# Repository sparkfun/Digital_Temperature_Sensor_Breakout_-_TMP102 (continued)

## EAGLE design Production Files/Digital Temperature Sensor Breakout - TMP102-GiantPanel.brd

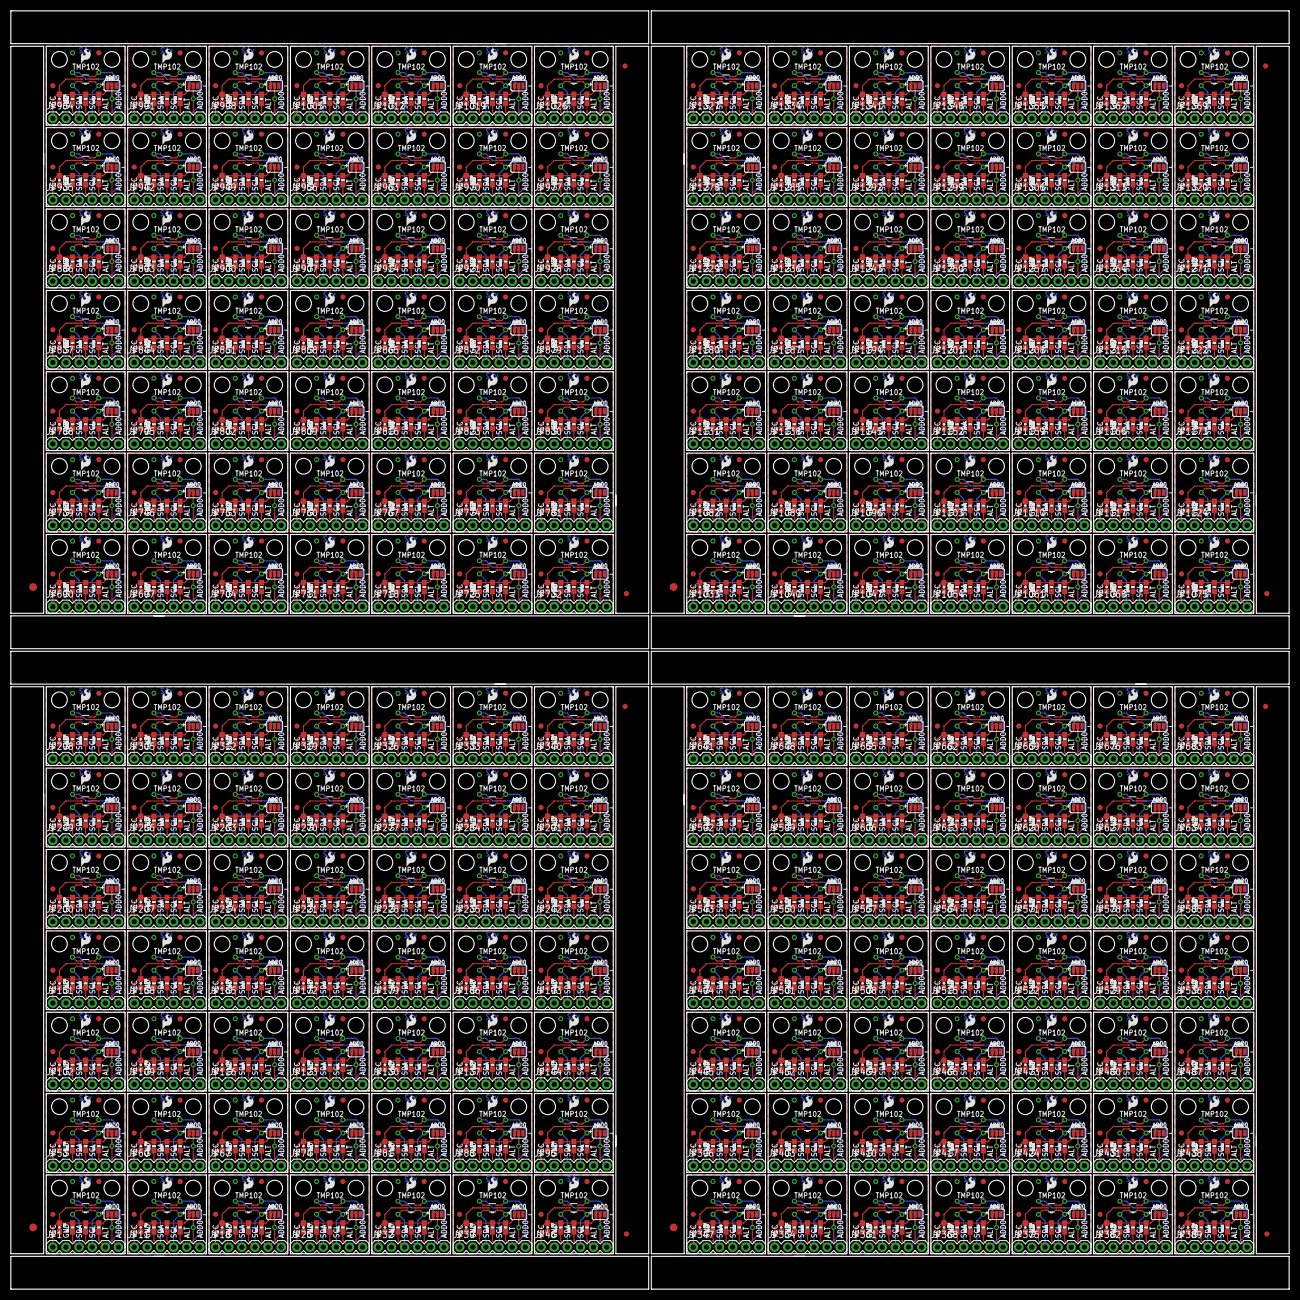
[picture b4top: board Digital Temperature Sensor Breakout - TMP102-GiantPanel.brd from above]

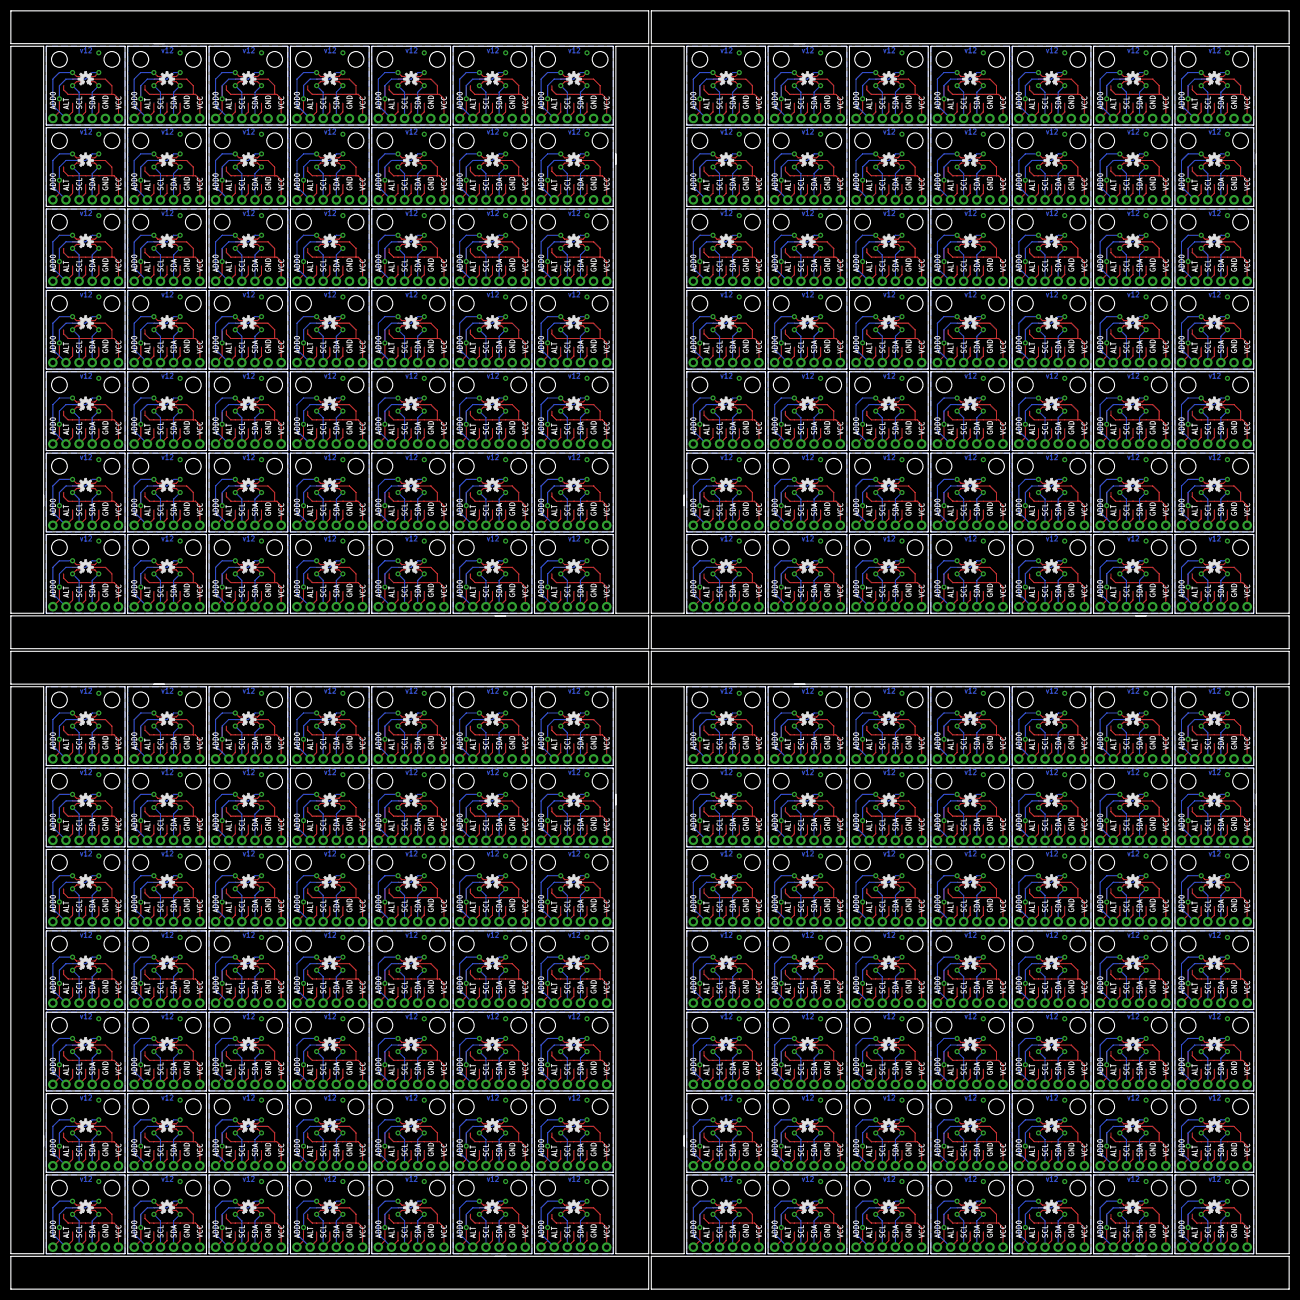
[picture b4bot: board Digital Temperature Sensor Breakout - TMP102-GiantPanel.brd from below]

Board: 2 copper layers, 247.4 x 247.4 mm, 2560 parts (196 on the bottom side), 1176 nets.

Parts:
C1, C2, C3, C4, C5, C6, C7, C8, C9, C10, C11, C12, C13, C14, C15, C16, C17, C18, C19, C20, C21, C22, C23, C24, C25, C26, C27, C28, C29, C30, C31, C32, C33, C34, C35, C36, C37, C38, C39, C40, C41, C42, C43, C44, C45, C46, C47, C48, C49, C50, C51, C52, C53, C54, C55, C56, C57, C58, C59, C60, C61, C62, C63, C64, C65, C66, C67, C68, C69, C70, C71, C72, C73, C74, C75, C76, C77, C78, C79, C80, C81, C82, C83, C84, C85, C86, C87, C88, C89, C90, C91, C92, C93, C94, C95, C96, C97, C98, C99, C100, C101, C102, C103, C104, C105, C106, C107, C108, C109, C110, C111, C112, C113, C114, C115, C116, C117, C118, C119, C120, C121, C122, C123, C124, C125, C126, C127, C128, C129, C130, C131, C132, C133, C134, C135, C136, C137, C138, C139, C140, C141, C142, C143, C144, C145, C146, C147, C148, C149, C150, C151, C152, C153, C154, C155, C156, C157, C158, C159, C160, C161, C162, C163, C164, C165, C166, C167, C168, C169, C170, C171, C172, C173, C174, C175, C176, C177, C178, C179, C180, C181, C182, C183, C184, C185, C186, C187, C188, C189, C190, C191, C192, C193, C194, C195, C196: 0.1uF; 0603-CAP
E$1, E$6, E$9, E$12: FIDUCIAL-1.5X3
E$2, E$3, E$4, E$5, E$7, E$8, E$10, E$11: FIDUCIAL-1X2
JP1, JP11, JP18, JP25, JP32, JP39, JP46, JP53, JP60, JP67, JP74, JP81, JP88, JP95, JP102, JP109, JP116, JP123, JP130, JP137, JP144, JP151, JP158, JP165, JP172, JP179, JP186, JP193, JP200, JP207, JP214, JP221, JP228, JP235, JP242, JP249, JP256, JP263, JP270, JP277, JP284, JP291, JP298, JP305, JP312, JP319, JP326, JP333, JP340, JP347, JP354, JP361, JP368, JP375, JP382, JP389, JP396, JP403, JP410, JP417, JP424, JP431, JP438, JP445, JP452, JP459, JP466, JP473, JP480, JP487, JP494, JP501, JP508, JP515, JP522, JP529, JP536, JP543, JP550, JP557, JP564, JP571, JP578, JP585, JP592, JP599, JP606, JP613, JP620, JP627, JP634, JP641, JP648, JP655, JP662, JP669, JP676, JP683, JP690, JP697, JP704, JP711, JP718, JP725, JP732, JP739, JP746, JP753, JP760, JP767, JP774, JP781, JP788, JP795, JP802, JP809, JP816, JP823, JP830, JP837, JP844, JP851, JP858, JP865, JP872, JP879, JP886, JP893, JP900, JP907, JP914, JP921, JP928, JP935, JP942, JP949, JP956, JP963, JP970, JP977, JP984, JP991, JP998, JP1005, JP1012, JP1019, JP1026, JP1033, JP1040, JP1047, JP1054, JP1061, JP1068, JP1075, JP1082, JP1089, JP1096, JP1103, JP1110, JP1117, JP1124, JP1131, JP1138, JP1145, JP1152, JP1159, JP1166, JP1173, JP1180, JP1187, JP1194, JP1201, JP1208, JP1215, JP1222, JP1229, JP1236, JP1243, JP1250, JP1257, JP1264, JP1271, JP1278, JP1285, JP1292, JP1299, JP1306, JP1313, JP1320, JP1327, JP1334, JP1341, JP1348, JP1355, JP1362, JP1369: 1X06
JP2, JP12, JP19, JP26, JP33, JP40, JP47, JP54, JP61, JP68, JP75, JP82, JP89, JP96, JP103, JP110, JP117, JP124, JP131, JP138, JP145, JP152, JP159, JP166, JP173, JP180, JP187, JP194, JP201, JP208, JP215, JP222, JP229, JP236, JP243, JP250, JP257, JP264, JP271, JP278, JP285, JP292, JP299, JP306, JP313, JP320, JP327, JP334, JP341, JP348, JP355, JP362, JP369, JP376, JP383, JP390, JP397, JP404, JP411, JP418, JP425, JP432, JP439, JP446, JP453, JP460, JP467, JP474, JP481, JP488, JP495, JP502, JP509, JP516, JP523, JP530, JP537, JP544, JP551, JP558, JP565, JP572, JP579, JP586, JP593, JP600, JP607, JP614, JP621, JP628, JP635, JP642, JP649, JP656, JP663, JP670, JP677, JP684, JP691, JP698, JP705, JP712, JP719, JP726, JP733, JP740, JP747, JP754, JP761, JP768, JP775, JP782, JP789, JP796, JP803, JP810, JP817, JP824, JP831, JP838, JP845, JP852, JP859, JP866, JP873, JP880, JP887, JP894, JP901, JP908, JP915, JP922, JP929, JP936, JP943, JP950, JP957, JP964, JP971, JP978, JP985, JP992, JP999, JP1006, JP1013, JP1020, JP1027, JP1034, JP1041, JP1048, JP1055, JP1062, JP1069, JP1076, JP1083, JP1090, JP1097, JP1104, JP1111, JP1118, JP1125, JP1132, JP1139, JP1146, JP1153, JP1160, JP1167, JP1174, JP1181, JP1188, JP1195, JP1202, JP1209, JP1216, JP1223, JP1230, JP1237, JP1244, JP1251, JP1258, JP1265, JP1272, JP1279, JP1286, JP1293, JP1300, JP1307, JP1314, JP1321, JP1328, JP1335, JP1342, JP1349, JP1356, JP1363, JP1370: JUMPER-32-3; SJ_3_PASTE2&3
JP3, JP8, JP15, JP22, JP29, JP36, JP43, JP50, JP57, JP64, JP71, JP78, JP85, JP92, JP99, JP106, JP113, JP120, JP127, JP134, JP141, JP148, JP155, JP162, JP169, JP176, JP183, JP190, JP197, JP204, JP211, JP218, JP225, JP232, JP239, JP246, JP253, JP260, JP267, JP274, JP281, JP288, JP295, JP302, JP309, JP316, JP323, JP330, JP337, JP344, JP351, JP358, JP365, JP372, JP379, JP386, JP393, JP400, JP407, JP414, JP421, JP428, JP435, JP442, JP449, JP456, JP463, JP470, JP477, JP484, JP491, JP498, JP505, JP512, JP519, JP526, JP533, JP540, JP547, JP554, JP561, JP568, JP575, JP582, JP589, JP596, JP603, JP610, JP617, JP624, JP631, JP638, JP645, JP652, JP659, JP666, JP673, JP680, JP687, JP694, JP701, JP708, JP715, JP722, JP729, JP736, JP743, JP750, JP757, JP764, JP771, JP778, JP785, JP792, JP799, JP806, JP813, JP820, JP827, JP834, JP841, JP848, JP855, JP862, JP869, JP876, JP883, JP890, JP897, JP904, JP911, JP918, JP925, JP932, JP939, JP946, JP953, JP960, JP967, JP974, JP981, JP988, JP995, JP1002, JP1009, JP1016, JP1023, JP1030, JP1037, JP1044, JP1051, JP1058, JP1065, JP1072, JP1079, JP1086, JP1093, JP1100, JP1107, JP1114, JP1121, JP1128, JP1135, JP1142, JP1149, JP1156, JP1163, JP1170, JP1177, JP1184, JP1191, JP1198, JP1205, JP1212, JP1219, JP1226, JP1233, JP1240, JP1247, JP1254, JP1261, JP1268, JP1275, JP1282, JP1289, JP1296, JP1303, JP1310, JP1317, JP1324, JP1331, JP1338, JP1345, JP1352, JP1359, JP1366: LOGO-SFESK; SFE-LOGO-FLAME
JP4, JP5, JP9, JP10, JP16, JP17, JP23, JP24, JP30, JP31, JP37, JP38, JP44, JP45, JP51, JP52, JP58, JP59, JP65, JP66, JP72, JP73, JP79, JP80, JP86, JP87, JP93, JP94, JP100, JP101, JP107, JP108, JP114, JP115, JP121, JP122, JP128, JP129, JP135, JP136, JP142, JP143, JP149, JP150, JP156, JP157, JP163, JP164, JP170, JP171, JP177, JP178, JP184, JP185, JP191, JP192, JP198, JP199, JP205, JP206, JP212, JP213, JP219, JP220, JP226, JP227, JP233, JP234, JP240, JP241, JP247, JP248, JP254, JP255, JP261, JP262, JP268, JP269, JP275, JP276, JP282, JP283, JP289, JP290, JP296, JP297, JP303, JP304, JP310, JP311, JP317, JP318, JP324, JP325, JP331, JP332, JP338, JP339, JP345, JP346, JP352, JP353, JP359, JP360, JP366, JP367, JP373, JP374, JP380, JP381, JP387, JP388, JP394, JP395, JP401, JP402, JP408, JP409, JP415, JP416, JP422, JP423, JP429, JP430, JP436, JP437, JP443, JP444, JP450, JP451, JP457, JP458, JP464, JP465, JP471, JP472, JP478, JP479, JP485, JP486, JP492, JP493, JP499, JP500, JP506, JP507, JP513, JP514, JP520, JP521, JP527, JP528, JP534, JP535, JP541, JP542, JP548, JP549, JP555, JP556, JP562, JP563, JP569, JP570, JP576, JP577, JP583, JP584, JP590, JP591, JP597, JP598, JP604, JP605, JP611, JP612, JP618, JP619, JP625, JP626, JP632, JP633, JP639, JP640, JP646, JP647, JP653, JP654, JP660, JP661, JP667, JP668, JP674, JP675, JP681, JP682, JP688, JP689, JP695, JP696, JP702, JP703, JP709, JP710, JP716, JP717, JP723, JP724, JP730, JP731, JP737, JP738, JP744, JP745, JP751, JP752, JP758, JP759, JP765, JP766, JP772, JP773, JP779, JP780, JP786, JP787, JP793, JP794, JP800, JP801, JP807, JP808, JP814, JP815, JP821, JP822, JP828, JP829, JP835, JP836, JP842, JP843, JP849, JP850, JP856, JP857, JP863, JP864, JP870, JP871, JP877, JP878, JP884, JP885, JP891, JP892, JP898, JP899, JP905, JP906, JP912, JP913, JP919, JP920, JP926, JP927, JP933, JP934, JP940, JP941, JP947, JP948, JP954, JP955, JP961, JP962, JP968, JP969, JP975, JP976, JP982, JP983, JP989, JP990, JP996, JP997, JP1003, JP1004, JP1010, JP1011, JP1017, JP1018, JP1024, JP1025, JP1031, JP1032, JP1038, JP1039, JP1045, JP1046, JP1052, JP1053, JP1059, JP1060, JP1066, JP1067, JP1073, JP1074, JP1080, JP1081, JP1087, JP1088, JP1094, JP1095, JP1101, JP1102, JP1108, JP1109, JP1115, JP1116, JP1122, JP1123, JP1129, JP1130, JP1136, JP1137, JP1143, JP1144, JP1150, JP1151, JP1157, JP1158, JP1164, JP1165, JP1171, JP1172, JP1178, JP1179, JP1185, JP1186, JP1192, JP1193, JP1199, JP1200, JP1206, JP1207, JP1213, JP1214, JP1220, JP1221, JP1227, JP1228, JP1234, JP1235, JP1241, JP1242, JP1248, JP1249, JP1255, JP1256, JP1262, JP1263, JP1269, JP1270, JP1276, JP1277, JP1283, JP1284, JP1290, JP1291, JP1297, JP1298, JP1304, JP1305, JP1311, JP1312, JP1318, JP1319, JP1325, JP1326, JP1332, JP1333, JP1339, JP1340, JP1346, JP1347, JP1353, JP1354, JP1360, JP1361, JP1367, JP1368: FIDUCIAL1X2; FIDUCIAL-1X2
JP6, JP7, JP13, JP14, JP20, JP21, JP27, JP28, JP34, JP35, JP41, JP42, JP48, JP49, JP55, JP56, JP62, JP63, JP69, JP70, JP76, JP77, JP83, JP84, JP90, JP91, JP97, JP98, JP104, JP105, JP111, JP112, JP118, JP119, JP125, JP126, JP132, JP133, JP139, JP140, JP146, JP147, JP153, JP154, JP160, JP161, JP167, JP168, JP174, JP175, JP181, JP182, JP188, JP189, JP195, JP196, JP202, JP203, JP209, JP210, JP216, JP217, JP223, JP224, JP230, JP231, JP237, JP238, JP244, JP245, JP251, JP252, JP258, JP259, JP265, JP266, JP272, JP273, JP279, JP280, JP286, JP287, JP293, JP294, JP300, JP301, JP307, JP308, JP314, JP315, JP321, JP322, JP328, JP329, JP335, JP336, JP342, JP343, JP349, JP350, JP356, JP357, JP363, JP364, JP370, JP371, JP377, JP378, JP384, JP385, JP391, JP392, JP398, JP399, JP405, JP406, JP412, JP413, JP419, JP420, JP426, JP427, JP433, JP434, JP440, JP441, JP447, JP448, JP454, JP455, JP461, JP462, JP468, JP469, JP475, JP476, JP482, JP483, JP489, JP490, JP496, JP497, JP503, JP504, JP510, JP511, JP517, JP518, JP524, JP525, JP531, JP532, JP538, JP539, JP545, JP546, JP552, JP553, JP559, JP560, JP566, JP567, JP573, JP574, JP580, JP581, JP587, JP588, JP594, JP595, JP601, JP602, JP608, JP609, JP615, JP616, JP622, JP623, JP629, JP630, JP636, JP637, JP643, JP644, JP650, JP651, JP657, JP658, JP664, JP665, JP671, JP672, JP678, JP679, JP685, JP686, JP692, JP693, JP699, JP700, JP706, JP707, JP713, JP714, JP720, JP721, JP727, JP728, JP734, JP735, JP741, JP742, JP748, JP749, JP755, JP756, JP762, JP763, JP769, JP770, JP776, JP777, JP783, JP784, JP790, JP791, JP797, JP798, JP804, JP805, JP811, JP812, JP818, JP819, JP825, JP826, JP832, JP833, JP839, JP840, JP846, JP847, JP853, JP854, JP860, JP861, JP867, JP868, JP874, JP875, JP881, JP882, JP888, JP889, JP895, JP896, JP902, JP903, JP909, JP910, JP916, JP917, JP923, JP924, JP930, JP931, JP937, JP938, JP944, JP945, JP951, JP952, JP958, JP959, JP965, JP966, JP972, JP973, JP979, JP980, JP986, JP987, JP993, JP994, JP1000, JP1001, JP1007, JP1008, JP1014, JP1015, JP1021, JP1022, JP1028, JP1029, JP1035, JP1036, JP1042, JP1043, JP1049, JP1050, JP1056, JP1057, JP1063, JP1064, JP1070, JP1071, JP1077, JP1078, JP1084, JP1085, JP1091, JP1092, JP1098, JP1099, JP1105, JP1106, JP1112, JP1113, JP1119, JP1120, JP1126, JP1127, JP1133, JP1134, JP1140, JP1141, JP1147, JP1148, JP1154, JP1155, JP1161, JP1162, JP1168, JP1169, JP1175, JP1176, JP1182, JP1183, JP1189, JP1190, JP1196, JP1197, JP1203, JP1204, JP1210, JP1211, JP1217, JP1218, JP1224, JP1225, JP1231, JP1232, JP1238, JP1239, JP1245, JP1246, JP1252, JP1253, JP1259, JP1260, JP1266, JP1267, JP1273, JP1274, JP1280, JP1281, JP1287, JP1288, JP1294, JP1295, JP1301, JP1302, JP1308, JP1309, JP1315, JP1316, JP1322, JP1323, JP1329, JP1330, JP1336, JP1337, JP1343, JP1344, JP1350, JP1351, JP1357, JP1358, JP1364, JP1365, JP1371, JP1372: STAND-OFFTIGHT; STAND-OFF-TIGHT
R1, R2, R3, R4, R5, R6, R7, R8, R9, R10, R11, R12, R13, R14, R15, R16, R17, R18, R19, R20, R21, R22, R23, R24, R25, R26, R27, R28, R29, R30, R31, R32, R33, R34, R35, R36, R37, R38, R39, R40, R41, R42, R43, R44, R45, R46, R47, R48, R49, R50, R51, R52, R53, R54, R55, R56, R57, R58, R59, R60, R61, R62, R63, R64, R65, R66, R67, R68, R69, R70, R71, R72, R73, R74, R75, R76, R77, R78, R79, R80, R81, R82, R83, R84, R85, R86, R87, R88, R89, R90, R91, R92, R93, R94, R95, R96, R97, R98, R99, R100, R101, R102, R103, R104, R105, R106, R107, R108, R109, R110, R111, R112, R113, R114, R115, R116, R117, R118, R119, R120, R121, R122, R123, R124, R125, R126, R127, R128, R129, R130, R131, R132, R133, R134, R135, R136, R137, R138, R139, R140, R141, R142, R143, R144, R145, R146, R147, R148, R149, R150, R151, R152, R153, R154, R155, R156, R157, R158, R159, R160, R161, R162, R163, R164, R165, R166, R167, R168, R169, R170, R171, R172, R173, R174, R175, R176, R177, R178, R179, R180, R181, R182, R183, R184, R185, R186, R187, R188, R189, R190, R191, R192, R193, R194, R195, R196, R197, R198, R199, R200, R201, R202, R203, R204, R205, R206, R207, R208, R209, R210, R211, R212, R213, R214, R215, R216, R217, R218, R219, R220, R221, R222, R223, R224, R225, R226, R227, R228, R229, R230, R231, R232, R233, R234, R235, R236, R237, R238, R239, R240, R241, R242, R243, R244, R245, R246, R247, R248, R249, R250, R251, R252, R253, R254, R255, R256, R257, R258, R259, R260, R261, R262, R263, R264, R265, R266, R267, R268, R269, R270, R271, R272, R273, R274, R275, R276, R277, R278, R279, R280, R281, R282, R283, R284, R285, R286, R287, R288, R289, R290, R291, R292, R293, R294, R295, R296, R297, R298, R299, R300, R301, R302, R303, R304, R305, R306, R307, R308, R309, R310, R311, R312, R313, R314, R315, R316, R317, R318, R319, R320, R321, R322, R323, R324, R325, R326, R327, R328, R329, R330, R331, R332, R333, R334, R335, R336, R337, R338, R339, R340, R341, R342, R343, R344, R345, R346, R347, R348, R349, R350, R351, R352, R353, R354, R355, R356, R357, R358, R359, R360, R361, R362, R363, R364, R365, R366, R367, R368, R369, R370, R371, R372, R373, R374, R375, R376, R377, R378, R379, R380, R381, R382, R383, R384, R385, R386, R387, R388, R389, R390, R391, R392, R393, R394, R395, R396, R397, R398, R399, R400, R401, R402, R403, R404, R405, R406, R407, R408, R409, R410, R411, R412, R413, R414, R415, R416, R417, R418, R419, R420, R421, R422, R423, R424, R425, R426, R427, R428, R429, R430, R431, R432, R433, R434, R435, R436, R437, R438, R439, R440, R441, R442, R443, R444, R445, R446, R447, R448, R449, R450, R451, R452, R453, R454, R455, R456, R457, R458, R459, R460, R461, R462, R463, R464, R465, R466, R467, R468, R469, R470, R471, R472, R473, R474, R475, R476, R477, R478, R479, R480, R481, R482, R483, R484, R485, R486, R487, R488, R489, R490, R491, R492, R493, R494, R495, R496, R497, R498, R499, R500, R501, R502, R503, R504, R505, R506, R507, R508, R509, R510, R511, R512, R513, R514, R515, R516, R517, R518, R519, R520, R521, R522, R523, R524, R525, R526, R527, R528, R529, R530, R531, R532, R533, R534, R535, R536, R537, R538, R539, R540, R541, R542, R543, R544, R545, R546, R547, R548, R549, R550, R551, R552, R553, R554, R555, R556, R557, R558, R559, R560, R561, R562, R563, R564, R565, R566, R567, R568, R569, R570, R571, R572, R573, R574, R575, R576, R577, R578, R579, R580, R581, R582, R583, R584, R585, R586, R587, R588: 1K; 0603-RES
U1, U2, U3, U4, U5, U6, U7, U8, U9, U10, U11, U12, U13, U14, U15, U16, U17, U18, U19, U20, U21, U22, U23, U24, U25, U26, U27, U28, U29, U30, U31, U32, U33, U34, U35, U36, U37, U38, U39, U40, U41, U42, U43, U44, U45, U46, U47, U48, U49, U50, U51, U52, U53, U54, U55, U56, U57, U58, U59, U60, U61, U62, U63, U64, U65, U66, U67, U68, U69, U70, U71, U72, U73, U74, U75, U76, U77, U78, U79, U80, U81, U82, U83, U84, U85, U86, U87, U88, U89, U90, U91, U92, U93, U94, U95, U96, U97, U98, U99, U100, U101, U102, U103, U104, U105, U106, U107, U108, U109, U110, U111, U112, U113, U114, U115, U116, U117, U118, U119, U120, U121, U122, U123, U124, U125, U126, U127, U128, U129, U130, U131, U132, U133, U134, U135, U136, U137, U138, U139, U140, U141, U142, U143, U144, U145, U146, U147, U148, U149, U150, U151, U152, U153, U154, U155, U156, U157, U158, U159, U160, U161, U162, U163, U164, U165, U166, U167, U168, U169, U170, U171, U172, U173, U174, U175, U176, U177, U178, U179, U180, U181, U182, U183, U184, U185, U186, U187, U188, U189, U190, U191, U192, U193, U194, U195, U196: TMP1021:1; SOT563-2
U$1, U$2, U$3, U$4, U$5, U$6, U$7, U$8, U$9, U$10, U$11, U$12, U$13, U$14, U$15, U$16, U$17, U$18, U$19, U$20, U$21, U$22, U$23, U$24, U$25, U$26, U$27, U$28, U$29, U$30, U$31, U$32, U$33, U$34, U$35, U$36, U$37, U$38, U$39, U$40, U$41, U$42, U$43, U$44, U$45, U$46, U$47, U$48, U$49, U$50, U$51, U$52, U$53, U$54, U$55, U$56, U$57, U$58, U$59, U$60, U$61, U$62, U$63, U$64, U$65, U$66, U$67, U$68, U$69, U$70, U$71, U$72, U$73, U$74, U$75, U$76, U$77, U$78, U$79, U$80, U$81, U$82, U$83, U$84, U$85, U$86, U$87, U$88, U$89, U$90, U$91, U$92, U$93, U$94, U$95, U$96, U$97, U$98, U$99, U$100, U$101, U$102, U$103, U$104, U$105, U$106, U$107, U$108, U$109, U$110, U$111, U$112, U$113, U$114, U$115, U$116, U$117, U$118, U$119, U$120, U$121, U$122, U$123, U$124, U$125, U$126, U$127, U$128, U$129, U$130, U$131, U$132, U$133, U$134, U$135, U$136, U$137, U$138, U$139, U$140, U$141, U$142, U$143, U$144, U$145, U$146, U$147, U$148, U$149, U$150, U$151, U$152, U$153, U$154, U$155, U$156, U$157, U$158, U$159, U$160, U$161, U$162, U$163, U$164, U$165, U$166, U$167, U$168, U$169, U$170, U$171, U$172, U$173, U$174, U$175, U$176, U$177, U$178, U$179, U$180, U$181, U$182, U$183, U$184, U$185, U$186, U$187, U$188, U$189, U$190, U$191, U$192, U$193, U$194, U$195, U$196: OSHW-LOGO-S

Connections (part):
ADD0: JP1.6, JP2.2, U1.4
ADD1: JP11.6, JP12.2, U2.4
ADD2: JP18.6, JP19.2, U3.4
ADD3: JP25.6, JP26.2, U4.4
ADD4: JP32.6, JP33.2, U5.4
ADD5: JP39.6, JP40.2, U6.4
ADD6: JP46.6, JP47.2, U7.4
ADD7: JP53.6, JP54.2, U8.4
ADD8: JP60.6, JP61.2, U9.4
ADD9: JP67.6, JP68.2, U10.4
ADD10: JP74.6, JP75.2, U11.4
ADD11: JP81.6, JP82.2, U12.4
ADD12: JP88.6, JP89.2, U13.4
ADD13: JP95.6, JP96.2, U14.4
ADD14: JP102.6, JP103.2, U15.4
ADD15: JP109.6, JP110.2, U16.4
ADD16: JP116.6, JP117.2, U17.4
ADD17: JP123.6, JP124.2, U18.4
ADD18: JP130.6, JP131.2, U19.4
ADD19: JP137.6, JP138.2, U20.4
ADD20: JP144.6, JP145.2, U21.4
ADD21: JP151.6, JP152.2, U22.4
ADD22: JP158.6, JP159.2, U23.4
ADD23: JP165.6, JP166.2, U24.4
ADD24: JP172.6, JP173.2, U25.4
ADD25: JP179.6, JP180.2, U26.4
ADD26: JP186.6, JP187.2, U27.4
ADD27: JP193.6, JP194.2, U28.4
ADD28: JP200.6, JP201.2, U29.4
ADD29: JP207.6, JP208.2, U30.4
ADD30: JP214.6, JP215.2, U31.4
ADD31: JP221.6, JP222.2, U32.4
ADD32: JP228.6, JP229.2, U33.4
ADD33: JP235.6, JP236.2, U34.4
ADD34: JP242.6, JP243.2, U35.4
ADD35: JP249.6, JP250.2, U36.4
ADD36: JP256.6, JP257.2, U37.4
ADD37: JP263.6, JP264.2, U38.4
ADD38: JP270.6, JP271.2, U39.4
ADD39: JP277.6, JP278.2, U40.4
ADD40: JP284.6, JP285.2, U41.4
ADD41: JP291.6, JP292.2, U42.4
ADD42: JP298.6, JP299.2, U43.4
ADD43: JP305.6, JP306.2, U44.4
ADD44: JP312.6, JP313.2, U45.4
ADD45: JP319.6, JP320.2, U46.4
ADD46: JP326.6, JP327.2, U47.4
ADD47: JP333.6, JP334.2, U48.4
ADD48: JP340.6, JP341.2, U49.4
ADD49: JP347.6, JP348.2, U50.4
ADD50: JP354.6, JP355.2, U51.4
ADD51: JP361.6, JP362.2, U52.4
ADD52: JP368.6, JP369.2, U53.4
ADD53: JP375.6, JP376.2, U54.4
ADD54: JP382.6, JP383.2, U55.4
ADD55: JP389.6, JP390.2, U56.4
ADD56: JP396.6, JP397.2, U57.4
ADD57: JP403.6, JP404.2, U58.4
ADD58: JP410.6, JP411.2, U59.4
ADD59: JP417.6, JP418.2, U60.4
ADD60: JP424.6, JP425.2, U61.4
ADD61: JP431.6, JP432.2, U62.4
ADD62: JP438.6, JP439.2, U63.4
ADD63: JP445.6, JP446.2, U64.4
ADD64: JP452.6, JP453.2, U65.4
ADD65: JP459.6, JP460.2, U66.4
ADD66: JP466.6, JP467.2, U67.4
ADD67: JP473.6, JP474.2, U68.4
ADD68: JP480.6, JP481.2, U69.4
ADD69: JP487.6, JP488.2, U70.4
ADD70: JP494.6, JP495.2, U71.4
ADD71: JP501.6, JP502.2, U72.4
ADD72: JP508.6, JP509.2, U73.4
ADD73: JP515.6, JP516.2, U74.4
ADD74: JP522.6, JP523.2, U75.4
ADD75: JP529.6, JP530.2, U76.4
ADD76: JP536.6, JP537.2, U77.4
ADD77: JP543.6, JP544.2, U78.4
ADD78: JP550.6, JP551.2, U79.4
ADD79: JP557.6, JP558.2, U80.4
ADD80: JP564.6, JP565.2, U81.4
ADD81: JP571.6, JP572.2, U82.4
ADD82: JP578.6, JP579.2, U83.4
ADD83: JP585.6, JP586.2, U84.4
ADD84: JP592.6, JP593.2, U85.4
ADD85: JP599.6, JP600.2, U86.4
ADD86: JP606.6, JP607.2, U87.4
ADD87: JP613.6, JP614.2, U88.4
ADD88: JP620.6, JP621.2, U89.4
ADD89: JP627.6, JP628.2, U90.4
ADD90: JP634.6, JP635.2, U91.4
ADD91: JP641.6, JP642.2, U92.4
ADD92: JP648.6, JP649.2, U93.4
ADD93: JP655.6, JP656.2, U94.4
ADD94: JP662.6, JP663.2, U95.4
ADD95: JP669.6, JP670.2, U96.4
ADD96: JP676.6, JP677.2, U97.4
ADD97: JP683.6, JP684.2, U98.4
ADD98: JP690.6, JP691.2, U99.4
ADD99: JP697.6, JP698.2, U100.4
ADD100: JP704.6, JP705.2, U101.4
ADD101: JP711.6, JP712.2, U102.4
ADD102: JP718.6, JP719.2, U103.4
ADD103: JP725.6, JP726.2, U104.4
ADD104: JP732.6, JP733.2, U105.4
ADD105: JP739.6, JP740.2, U106.4
ADD106: JP746.6, JP747.2, U107.4
ADD107: JP753.6, JP754.2, U108.4
ADD108: JP760.6, JP761.2, U109.4
ADD109: JP767.6, JP768.2, U110.4
ADD110: JP774.6, JP775.2, U111.4
ADD111: JP781.6, JP782.2, U112.4
ADD112: JP788.6, JP789.2, U113.4
ADD113: JP795.6, JP796.2, U114.4
ADD114: JP802.6, JP803.2, U115.4
ADD115: JP809.6, JP810.2, U116.4
ADD116: JP816.6, JP817.2, U117.4
ADD117: JP823.6, JP824.2, U118.4
ADD118: JP830.6, JP831.2, U119.4
ADD119: JP837.6, JP838.2, U120.4
ADD120: JP844.6, JP845.2, U121.4
ADD121: JP851.6, JP852.2, U122.4
ADD122: JP858.6, JP859.2, U123.4
ADD123: JP865.6, JP866.2, U124.4
ADD124: JP872.6, JP873.2, U125.4
ADD125: JP879.6, JP880.2, U126.4
ADD126: JP886.6, JP887.2, U127.4
ADD127: JP893.6, JP894.2, U128.4
ADD128: JP900.6, JP901.2, U129.4
ADD129: JP907.6, JP908.2, U130.4
ADD130: JP914.6, JP915.2, U131.4
ADD131: JP921.6, JP922.2, U132.4
ADD132: JP928.6, JP929.2, U133.4
ADD133: JP935.6, JP936.2, U134.4
ADD134: JP942.6, JP943.2, U135.4
ADD135: JP949.6, JP950.2, U136.4
ADD136: JP956.6, JP957.2, U137.4
ADD137: JP963.6, JP964.2, U138.4
ADD138: JP970.6, JP971.2, U139.4
ADD139: JP977.6, JP978.2, U140.4
ADD140: JP984.6, JP985.2, U141.4
ADD141: JP991.6, JP992.2, U142.4
ADD142: JP998.6, JP999.2, U143.4
ADD143: JP1005.6, JP1006.2, U144.4
ADD144: JP1012.6, JP1013.2, U145.4
ADD145: JP1019.6, JP1020.2, U146.4
ADD146: JP1026.6, JP1027.2, U147.4
ADD147: JP1033.6, JP1034.2, U148.4
ADD148: JP1040.6, JP1041.2, U149.4
ADD149: JP1047.6, JP1048.2, U150.4
ADD150: JP1054.6, JP1055.2, U151.4
ADD151: JP1061.6, JP1062.2, U152.4
ADD152: JP1068.6, JP1069.2, U153.4
ADD153: JP1075.6, JP1076.2, U154.4
ADD154: JP1082.6, JP1083.2, U155.4
ADD155: JP1089.6, JP1090.2, U156.4
ADD156: JP1096.6, JP1097.2, U157.4
ADD157: JP1103.6, JP1104.2, U158.4
ADD158: JP1110.6, JP1111.2, U159.4
ADD159: JP1117.6, JP1118.2, U160.4
ADD160: JP1124.6, JP1125.2, U161.4
ADD161: JP1131.6, JP1132.2, U162.4
ADD162: JP1138.6, JP1139.2, U163.4
ADD163: JP1145.6, JP1146.2, U164.4
ADD164: JP1152.6, JP1153.2, U165.4
ADD165: JP1159.6, JP1160.2, U166.4
ADD166: JP1166.6, JP1167.2, U167.4
ADD167: JP1173.6, JP1174.2, U168.4
ADD168: JP1180.6, JP1181.2, U169.4
ADD169: JP1187.6, JP1188.2, U170.4
ADD170: JP1194.6, JP1195.2, U171.4
ADD171: JP1201.6, JP1202.2, U172.4
ADD172: JP1208.6, JP1209.2, U173.4
ADD173: JP1215.6, JP1216.2, U174.4
ADD174: JP1222.6, JP1223.2, U175.4
ADD175: JP1229.6, JP1230.2, U176.4
ADD176: JP1236.6, JP1237.2, U177.4
ADD177: JP1243.6, JP1244.2, U178.4
ADD178: JP1250.6, JP1251.2, U179.4
ADD179: JP1257.6, JP1258.2, U180.4
ADD180: JP1264.6, JP1265.2, U181.4
ADD181: JP1271.6, JP1272.2, U182.4
ADD182: JP1278.6, JP1279.2, U183.4
ADD183: JP1285.6, JP1286.2, U184.4
ADD184: JP1292.6, JP1293.2, U185.4
ADD185: JP1299.6, JP1300.2, U186.4
ADD186: JP1306.6, JP1307.2, U187.4
ADD187: JP1313.6, JP1314.2, U188.4
ADD188: JP1320.6, JP1321.2, U189.4
ADD189: JP1327.6, JP1328.2, U190.4
ADD190: JP1334.6, JP1335.2, U191.4
ADD191: JP1341.6, JP1342.2, U192.4
ADD192: JP1348.6, JP1349.2, U193.4
ADD193: JP1355.6, JP1356.2, U194.4
ADD194: JP1362.6, JP1363.2, U195.4
ADD195: JP1369.6, JP1370.2, U196.4
ALERT: JP1.5, R3.1, U1.3
ALERT1: JP11.5, R6.1, U2.3
ALERT2: JP18.5, R9.1, U3.3
ALERT3: JP25.5, R12.1, U4.3
ALERT4: JP32.5, R15.1, U5.3
ALERT5: JP39.5, R18.1, U6.3
ALERT6: JP46.5, R21.1, U7.3
ALERT7: JP53.5, R24.1, U8.3
ALERT8: JP60.5, R27.1, U9.3
ALERT9: JP67.5, R30.1, U10.3
ALERT10: JP74.5, R33.1, U11.3
ALERT11: JP81.5, R36.1, U12.3
ALERT12: JP88.5, R39.1, U13.3
ALERT13: JP95.5, R42.1, U14.3
ALERT14: JP102.5, R45.1, U15.3
ALERT15: JP109.5, R48.1, U16.3
ALERT16: JP116.5, R51.1, U17.3
ALERT17: JP123.5, R54.1, U18.3
ALERT18: JP130.5, R57.1, U19.3
ALERT19: JP137.5, R60.1, U20.3
ALERT20: JP144.5, R63.1, U21.3
ALERT21: JP151.5, R66.1, U22.3
ALERT22: JP158.5, R69.1, U23.3
ALERT23: JP165.5, R72.1, U24.3
ALERT24: JP172.5, R75.1, U25.3
ALERT25: JP179.5, R78.1, U26.3
ALERT26: JP186.5, R81.1, U27.3
ALERT27: JP193.5, R84.1, U28.3
ALERT28: JP200.5, R87.1, U29.3
ALERT29: JP207.5, R90.1, U30.3
ALERT30: JP214.5, R93.1, U31.3
ALERT31: JP221.5, R96.1, U32.3
ALERT32: JP228.5, R99.1, U33.3
ALERT33: JP235.5, R102.1, U34.3
ALERT34: JP242.5, R105.1, U35.3
ALERT35: JP249.5, R108.1, U36.3
ALERT36: JP256.5, R111.1, U37.3
ALERT37: JP263.5, R114.1, U38.3
ALERT38: JP270.5, R117.1, U39.3
ALERT39: JP277.5, R120.1, U40.3
ALERT40: JP284.5, R123.1, U41.3
ALERT41: JP291.5, R126.1, U42.3
ALERT42: JP298.5, R129.1, U43.3
ALERT43: JP305.5, R132.1, U44.3
ALERT44: JP312.5, R135.1, U45.3
ALERT45: JP319.5, R138.1, U46.3
ALERT46: JP326.5, R141.1, U47.3
ALERT47: JP333.5, R144.1, U48.3
ALERT48: JP340.5, R147.1, U49.3
ALERT49: JP347.5, R150.1, U50.3
ALERT50: JP354.5, R153.1, U51.3
ALERT51: JP361.5, R156.1, U52.3
ALERT52: JP368.5, R159.1, U53.3
ALERT53: JP375.5, R162.1, U54.3
ALERT54: JP382.5, R165.1, U55.3
ALERT55: JP389.5, R168.1, U56.3
ALERT56: JP396.5, R171.1, U57.3
ALERT57: JP403.5, R174.1, U58.3
ALERT58: JP410.5, R177.1, U59.3
ALERT59: JP417.5, R180.1, U60.3
ALERT60: JP424.5, R183.1, U61.3
ALERT61: JP431.5, R186.1, U62.3
ALERT62: JP438.5, R189.1, U63.3
ALERT63: JP445.5, R192.1, U64.3
ALERT64: JP452.5, R195.1, U65.3
ALERT65: JP459.5, R198.1, U66.3
ALERT66: JP466.5, R201.1, U67.3
ALERT67: JP473.5, R204.1, U68.3
ALERT68: JP480.5, R207.1, U69.3
ALERT69: JP487.5, R210.1, U70.3
ALERT70: JP494.5, R213.1, U71.3
ALERT71: JP501.5, R216.1, U72.3
ALERT72: JP508.5, R219.1, U73.3
ALERT73: JP515.5, R222.1, U74.3
ALERT74: JP522.5, R225.1, U75.3
ALERT75: JP529.5, R228.1, U76.3
ALERT76: JP536.5, R231.1, U77.3
ALERT77: JP543.5, R234.1, U78.3
ALERT78: JP550.5, R237.1, U79.3
ALERT79: JP557.5, R240.1, U80.3
ALERT80: JP564.5, R243.1, U81.3
ALERT81: JP571.5, R246.1, U82.3
ALERT82: JP578.5, R249.1, U83.3
ALERT83: JP585.5, R252.1, U84.3
ALERT84: JP592.5, R255.1, U85.3
ALERT85: JP599.5, R258.1, U86.3
ALERT86: JP606.5, R261.1, U87.3
ALERT87: JP613.5, R264.1, U88.3
ALERT88: JP620.5, R267.1, U89.3
ALERT89: JP627.5, R270.1, U90.3
ALERT90: JP634.5, R273.1, U91.3
ALERT91: JP641.5, R276.1, U92.3
ALERT92: JP648.5, R279.1, U93.3
ALERT93: JP655.5, R282.1, U94.3
ALERT94: JP662.5, R285.1, U95.3
ALERT95: JP669.5, R288.1, U96.3
ALERT96: JP676.5, R291.1, U97.3
ALERT97: JP683.5, R294.1, U98.3
ALERT98: JP690.5, R297.1, U99.3
ALERT99: JP697.5, R300.1, U100.3
ALERT100: JP704.5, R303.1, U101.3
ALERT101: JP711.5, R306.1, U102.3
ALERT102: JP718.5, R309.1, U103.3
ALERT103: JP725.5, R312.1, U104.3
ALERT104: JP732.5, R315.1, U105.3
ALERT105: JP739.5, R318.1, U106.3
ALERT106: JP746.5, R321.1, U107.3
ALERT107: JP753.5, R324.1, U108.3
ALERT108: JP760.5, R327.1, U109.3
ALERT109: JP767.5, R330.1, U110.3
ALERT110: JP774.5, R333.1, U111.3
ALERT111: JP781.5, R336.1, U112.3
ALERT112: JP788.5, R339.1, U113.3
ALERT113: JP795.5, R342.1, U114.3
ALERT114: JP802.5, R345.1, U115.3
ALERT115: JP809.5, R348.1, U116.3
ALERT116: JP816.5, R351.1, U117.3
ALERT117: JP823.5, R354.1, U118.3
ALERT118: JP830.5, R357.1, U119.3
ALERT119: JP837.5, R360.1, U120.3
ALERT120: JP844.5, R363.1, U121.3
ALERT121: JP851.5, R366.1, U122.3
ALERT122: JP858.5, R369.1, U123.3
ALERT123: JP865.5, R372.1, U124.3
ALERT124: JP872.5, R375.1, U125.3
ALERT125: JP879.5, R378.1, U126.3
ALERT126: JP886.5, R381.1, U127.3
ALERT127: JP893.5, R384.1, U128.3
ALERT128: JP900.5, R387.1, U129.3
ALERT129: JP907.5, R390.1, U130.3
ALERT130: JP914.5, R393.1, U131.3
ALERT131: JP921.5, R396.1, U132.3
ALERT132: JP928.5, R399.1, U133.3
ALERT133: JP935.5, R402.1, U134.3
ALERT134: JP942.5, R405.1, U135.3
ALERT135: JP949.5, R408.1, U136.3
ALERT136: JP956.5, R411.1, U137.3
ALERT137: JP963.5, R414.1, U138.3
ALERT138: JP970.5, R417.1, U139.3
ALERT139: JP977.5, R420.1, U140.3
ALERT140: JP984.5, R423.1, U141.3
ALERT141: JP991.5, R426.1, U142.3
ALERT142: JP998.5, R429.1, U143.3
ALERT143: JP1005.5, R432.1, U144.3
ALERT144: JP1012.5, R435.1, U145.3
ALERT145: JP1019.5, R438.1, U146.3
ALERT146: JP1026.5, R441.1, U147.3
ALERT147: JP1033.5, R444.1, U148.3
ALERT148: JP1040.5, R447.1, U149.3
ALERT149: JP1047.5, R450.1, U150.3
ALERT150: JP1054.5, R453.1, U151.3
ALERT151: JP1061.5, R456.1, U152.3
ALERT152: JP1068.5, R459.1, U153.3
ALERT153: JP1075.5, R462.1, U154.3
ALERT154: JP1082.5, R465.1, U155.3
ALERT155: JP1089.5, R468.1, U156.3
ALERT156: JP1096.5, R471.1, U157.3
ALERT157: JP1103.5, R474.1, U158.3
ALERT158: JP1110.5, R477.1, U159.3
ALERT159: JP1117.5, R480.1, U160.3
ALERT160: JP1124.5, R483.1, U161.3
ALERT161: JP1131.5, R486.1, U162.3
ALERT162: JP1138.5, R489.1, U163.3
ALERT163: JP1145.5, R492.1, U164.3
ALERT164: JP1152.5, R495.1, U165.3
ALERT165: JP1159.5, R498.1, U166.3
ALERT166: JP1166.5, R501.1, U167.3
ALERT167: JP1173.5, R504.1, U168.3
ALERT168: JP1180.5, R507.1, U169.3
ALERT169: JP1187.5, R510.1, U170.3
ALERT170: JP1194.5, R513.1, U171.3
ALERT171: JP1201.5, R516.1, U172.3
ALERT172: JP1208.5, R519.1, U173.3
ALERT173: JP1215.5, R522.1, U174.3
ALERT174: JP1222.5, R525.1, U175.3
ALERT175: JP1229.5, R528.1, U176.3
ALERT176: JP1236.5, R531.1, U177.3
ALERT177: JP1243.5, R534.1, U178.3
ALERT178: JP1250.5, R537.1, U179.3
ALERT179: JP1257.5, R540.1, U180.3
ALERT180: JP1264.5, R543.1, U181.3
ALERT181: JP1271.5, R546.1, U182.3
ALERT182: JP1278.5, R549.1, U183.3
ALERT183: JP1285.5, R552.1, U184.3
ALERT184: JP1292.5, R555.1, U185.3
ALERT185: JP1299.5, R558.1, U186.3
ALERT186: JP1306.5, R561.1, U187.3
ALERT187: JP1313.5, R564.1, U188.3
ALERT188: JP1320.5, R567.1, U189.3
ALERT189: JP1327.5, R570.1, U190.3
ALERT190: JP1334.5, R573.1, U191.3
ALERT191: JP1341.5, R576.1, U192.3
ALERT192: JP1348.5, R579.1, U193.3
ALERT193: JP1355.5, R582.1, U194.3
ALERT194: JP1362.5, R585.1, U195.3
ALERT195: JP1369.5, R588.1, U196.3
GND: C1.2, JP1.2, JP2.3, U1.2
GND1: C2.2, JP11.2, JP12.3, U2.2
GND2: C3.2, JP18.2, JP19.3, U3.2
GND3: C4.2, JP25.2, JP26.3, U4.2
GND4: C5.2, JP32.2, JP33.3, U5.2
GND5: C6.2, JP39.2, JP40.3, U6.2
GND6: C7.2, JP46.2, JP47.3, U7.2
GND7: C8.2, JP53.2, JP54.3, U8.2
GND8: C9.2, JP60.2, JP61.3, U9.2
GND9: C10.2, JP67.2, JP68.3, U10.2
GND10: C11.2, JP74.2, JP75.3, U11.2
GND11: C12.2, JP81.2, JP82.3, U12.2
GND12: C13.2, JP88.2, JP89.3, U13.2
GND13: C14.2, JP95.2, JP96.3, U14.2
GND14: C15.2, JP102.2, JP103.3, U15.2
GND15: C16.2, JP109.2, JP110.3, U16.2
GND16: C17.2, JP116.2, JP117.3, U17.2
GND17: C18.2, JP123.2, JP124.3, U18.2
GND18: C19.2, JP130.2, JP131.3, U19.2
GND19: C20.2, JP137.2, JP138.3, U20.2
GND20: C21.2, JP144.2, JP145.3, U21.2
GND21: C22.2, JP151.2, JP152.3, U22.2
GND22: C23.2, JP158.2, JP159.3, U23.2
GND23: C24.2, JP165.2, JP166.3, U24.2
GND24: C25.2, JP172.2, JP173.3, U25.2
GND25: C26.2, JP179.2, JP180.3, U26.2
GND26: C27.2, JP186.2, JP187.3, U27.2
GND27: C28.2, JP193.2, JP194.3, U28.2
GND28: C29.2, JP200.2, JP201.3, U29.2
GND29: C30.2, JP207.2, JP208.3, U30.2
GND30: C31.2, JP214.2, JP215.3, U31.2
GND31: C32.2, JP221.2, JP222.3, U32.2
GND32: C33.2, JP228.2, JP229.3, U33.2
GND33: C34.2, JP235.2, JP236.3, U34.2
GND34: C35.2, JP242.2, JP243.3, U35.2
GND35: C36.2, JP249.2, JP250.3, U36.2
GND36: C37.2, JP256.2, JP257.3, U37.2
GND37: C38.2, JP263.2, JP264.3, U38.2
GND38: C39.2, JP270.2, JP271.3, U39.2
GND39: C40.2, JP277.2, JP278.3, U40.2
GND40: C41.2, JP284.2, JP285.3, U41.2
GND41: C42.2, JP291.2, JP292.3, U42.2
GND42: C43.2, JP298.2, JP299.3, U43.2
GND43: C44.2, JP305.2, JP306.3, U44.2
GND44: C45.2, JP312.2, JP313.3, U45.2
GND45: C46.2, JP319.2, JP320.3, U46.2
GND46: C47.2, JP326.2, JP327.3, U47.2
GND47: C48.2, JP333.2, JP334.3, U48.2
GND48: C49.2, JP340.2, JP341.3, U49.2
GND49: C50.2, JP347.2, JP348.3, U50.2
GND50: C51.2, JP354.2, JP355.3, U51.2
GND51: C52.2, JP361.2, JP362.3, U52.2
GND52: C53.2, JP368.2, JP369.3, U53.2
GND53: C54.2, JP375.2, JP376.3, U54.2
GND54: C55.2, JP382.2, JP383.3, U55.2
GND55: C56.2, JP389.2, JP390.3, U56.2
GND56: C57.2, JP396.2, JP397.3, U57.2
GND57: C58.2, JP403.2, JP404.3, U58.2
GND58: C59.2, JP410.2, JP411.3, U59.2
GND59: C60.2, JP417.2, JP418.3, U60.2
GND60: C61.2, JP424.2, JP425.3, U61.2
GND61: C62.2, JP431.2, JP432.3, U62.2
GND62: C63.2, JP438.2, JP439.3, U63.2
GND63: C64.2, JP445.2, JP446.3, U64.2
GND64: C65.2, JP452.2, JP453.3, U65.2
GND65: C66.2, JP459.2, JP460.3, U66.2
GND66: C67.2, JP466.2, JP467.3, U67.2
GND67: C68.2, JP473.2, JP474.3, U68.2
GND68: C69.2, JP480.2, JP481.3, U69.2
GND69: C70.2, JP487.2, JP488.3, U70.2
GND70: C71.2, JP494.2, JP495.3, U71.2
GND71: C72.2, JP501.2, JP502.3, U72.2
GND72: C73.2, JP508.2, JP509.3, U73.2
GND73: C74.2, JP515.2, JP516.3, U74.2
GND74: C75.2, JP522.2, JP523.3, U75.2
GND75: C76.2, JP529.2, JP530.3, U76.2
GND76: C77.2, JP536.2, JP537.3, U77.2
GND77: C78.2, JP543.2, JP544.3, U78.2
GND78: C79.2, JP550.2, JP551.3, U79.2
GND79: C80.2, JP557.2, JP558.3, U80.2
GND80: C81.2, JP564.2, JP565.3, U81.2
GND81: C82.2, JP571.2, JP572.3, U82.2
GND82: C83.2, JP578.2, JP579.3, U83.2
GND83: C84.2, JP585.2, JP586.3, U84.2
GND84: C85.2, JP592.2, JP593.3, U85.2
GND85: C86.2, JP599.2, JP600.3, U86.2
GND86: C87.2, JP606.2, JP607.3, U87.2
GND87: C88.2, JP613.2, JP614.3, U88.2
GND88: C89.2, JP620.2, JP621.3, U89.2
GND89: C90.2, JP627.2, JP628.3, U90.2
GND90: C91.2, JP634.2, JP635.3, U91.2
GND91: C92.2, JP641.2, JP642.3, U92.2
GND92: C93.2, JP648.2, JP649.3, U93.2
GND93: C94.2, JP655.2, JP656.3, U94.2
GND94: C95.2, JP662.2, JP663.3, U95.2
GND95: C96.2, JP669.2, JP670.3, U96.2
GND96: C97.2, JP676.2, JP677.3, U97.2
GND97: C98.2, JP683.2, JP684.3, U98.2
GND98: C99.2, JP690.2, JP691.3, U99.2
GND99: C100.2, JP697.2, JP698.3, U100.2
GND100: C101.2, JP704.2, JP705.3, U101.2
GND101: C102.2, JP711.2, JP712.3, U102.2
GND102: C103.2, JP718.2, JP719.3, U103.2
GND103: C104.2, JP725.2, JP726.3, U104.2
GND104: C105.2, JP732.2, JP733.3, U105.2
GND105: C106.2, JP739.2, JP740.3, U106.2
GND106: C107.2, JP746.2, JP747.3, U107.2
GND107: C108.2, JP753.2, JP754.3, U108.2
GND108: C109.2, JP760.2, JP761.3, U109.2
GND109: C110.2, JP767.2, JP768.3, U110.2
GND110: C111.2, JP774.2, JP775.3, U111.2
GND111: C112.2, JP781.2, JP782.3, U112.2
GND112: C113.2, JP788.2, JP789.3, U113.2
GND113: C114.2, JP795.2, JP796.3, U114.2
GND114: C115.2, JP802.2, JP803.3, U115.2
GND115: C116.2, JP809.2, JP810.3, U116.2
GND116: C117.2, JP816.2, JP817.3, U117.2
GND117: C118.2, JP823.2, JP824.3, U118.2
GND118: C119.2, JP830.2, JP831.3, U119.2
GND119: C120.2, JP837.2, JP838.3, U120.2
GND120: C121.2, JP844.2, JP845.3, U121.2
GND121: C122.2, JP851.2, JP852.3, U122.2
GND122: C123.2, JP858.2, JP859.3, U123.2
GND123: C124.2, JP865.2, JP866.3, U124.2
GND124: C125.2, JP872.2, JP873.3, U125.2
GND125: C126.2, JP879.2, JP880.3, U126.2
GND126: C127.2, JP886.2, JP887.3, U127.2
GND127: C128.2, JP893.2, JP894.3, U128.2
GND128: C129.2, JP900.2, JP901.3, U129.2
GND129: C130.2, JP907.2, JP908.3, U130.2
GND130: C131.2, JP914.2, JP915.3, U131.2
GND131: C132.2, JP921.2, JP922.3, U132.2
GND132: C133.2, JP928.2, JP929.3, U133.2
GND133: C134.2, JP935.2, JP936.3, U134.2
GND134: C135.2, JP942.2, JP943.3, U135.2
GND135: C136.2, JP949.2, JP950.3, U136.2
GND136: C137.2, JP956.2, JP957.3, U137.2
GND137: C138.2, JP963.2, JP964.3, U138.2
GND138: C139.2, JP970.2, JP971.3, U139.2
GND139: C140.2, JP977.2, JP978.3, U140.2
GND140: C141.2, JP984.2, JP985.3, U141.2
GND141: C142.2, JP991.2, JP992.3, U142.2
GND142: C143.2, JP998.2, JP999.3, U143.2
GND143: C144.2, JP1005.2, JP1006.3, U144.2
GND144: C145.2, JP1012.2, JP1013.3, U145.2
GND145: C146.2, JP1019.2, JP1020.3, U146.2
GND146: C147.2, JP1026.2, JP1027.3, U147.2
GND147: C148.2, JP1033.2, JP1034.3, U148.2
GND148: C149.2, JP1040.2, JP1041.3, U149.2
GND149: C150.2, JP1047.2, JP1048.3, U150.2
GND150: C151.2, JP1054.2, JP1055.3, U151.2
GND151: C152.2, JP1061.2, JP1062.3, U152.2
GND152: C153.2, JP1068.2, JP1069.3, U153.2
GND153: C154.2, JP1075.2, JP1076.3, U154.2
GND154: C155.2, JP1082.2, JP1083.3, U155.2
GND155: C156.2, JP1089.2, JP1090.3, U156.2
GND156: C157.2, JP1096.2, JP1097.3, U157.2
GND157: C158.2, JP1103.2, JP1104.3, U158.2
GND158: C159.2, JP1110.2, JP1111.3, U159.2
GND159: C160.2, JP1117.2, JP1118.3, U160.2
GND160: C161.2, JP1124.2, JP1125.3, U161.2
GND161: C162.2, JP1131.2, JP1132.3, U162.2
GND162: C163.2, JP1138.2, JP1139.3, U163.2
GND163: C164.2, JP1145.2, JP1146.3, U164.2
GND164: C165.2, JP1152.2, JP1153.3, U165.2
GND165: C166.2, JP1159.2, JP1160.3, U166.2
GND166: C167.2, JP1166.2, JP1167.3, U167.2
GND167: C168.2, JP1173.2, JP1174.3, U168.2
GND168: C169.2, JP1180.2, JP1181.3, U169.2
GND169: C170.2, JP1187.2, JP1188.3, U170.2
GND170: C171.2, JP1194.2, JP1195.3, U171.2
GND171: C172.2, JP1201.2, JP1202.3, U172.2
GND172: C173.2, JP1208.2, JP1209.3, U173.2
GND173: C174.2, JP1215.2, JP1216.3, U174.2
GND174: C175.2, JP1222.2, JP1223.3, U175.2
GND175: C176.2, JP1229.2, JP1230.3, U176.2
GND176: C177.2, JP1236.2, JP1237.3, U177.2
GND177: C178.2, JP1243.2, JP1244.3, U178.2
GND178: C179.2, JP1250.2, JP1251.3, U179.2
GND179: C180.2, JP1257.2, JP1258.3, U180.2
GND180: C181.2, JP1264.2, JP1265.3, U181.2
GND181: C182.2, JP1271.2, JP1272.3, U182.2
GND182: C183.2, JP1278.2, JP1279.3, U183.2
GND183: C184.2, JP1285.2, JP1286.3, U184.2
GND184: C185.2, JP1292.2, JP1293.3, U185.2
GND185: C186.2, JP1299.2, JP1300.3, U186.2
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
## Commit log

2013-06-19 Initial commit of v12 board files
    1) 0402 to 0603 resistor footprint
    2) 1:1 main IC footprint
    3) Re-route traces directly away from IC
    4) Ver # in bottom copper
    5.) Added jumper for ADD0 select (default gnd)
    6.) Added mounting holes
2013-06-19 Renamed board files
    Renamed board files to match name of product on storefront. Also,
    replaced main IC device with properly named variant from updated library
    on github.
2013-06-24 Added better info in schematic
    Added a change log, version number, default i2c address info, and
    creative commons note to schematic.
2013-07-12 Created Giant Panel
    I've created the Gaint panel for the MYDATA which can then be broken
    down into 4 smaller panels that can be ran on the manncorp machines.
2013-07-12 Created Production Files folder
    I've moved the panels to the production files folder
2013-09-27 Updating to standard folder structure and license
    Changed Production Files folder to just Production and add gitattributes
    and license files.
2016-03-30 Revision 13 changes
    -Changed I2C address from 0x90 to 0x48.
    -Changed I2C pull-up values to 4.7k
    -Changed Alert pin pull-up to 4.7k
    -Added I2C pull-up solder jumper
    -Changed ADD0 pull-down jumper to 2-pad NC
    -Added table of I2C addresses based on ADD0 connection.
2016-04-06 Applied Fixes from Design Review
    -Moved traces on end of sensors to extend out the other way.
    -Added note in schematic about using an external jumper to change I2C
    address.
    -Removed Kade's name from document layer.
    -Added pull down resistor to prevent shorts with I2C address changes.
    -Added unit of measurement on Measures layer.
2016-04-12 QC Fixes
    Updated parts with PROD_ID attributes
2016-05-09 Rotated copper for version number
    Now matches with board silk.
2016-05-10 Changed file names
    replaced spaces with underscore
2016-05-11 deleting old panels
2016-05-11 created panel v13
2016-07-07 Updating Documentation
    -Adding datasheet
    -Adding example library and example code
    -Adding readmes, license, and git files
2016-07-08 Updating README
    - Updated links to new product page
    - Updated product images to v13
2016-07-27 Updating file names to follow standard
2016-08-15 Updated Libary
    Updated with the latest and greatest example library
2025-06-27 Update README.md
    Updating link
